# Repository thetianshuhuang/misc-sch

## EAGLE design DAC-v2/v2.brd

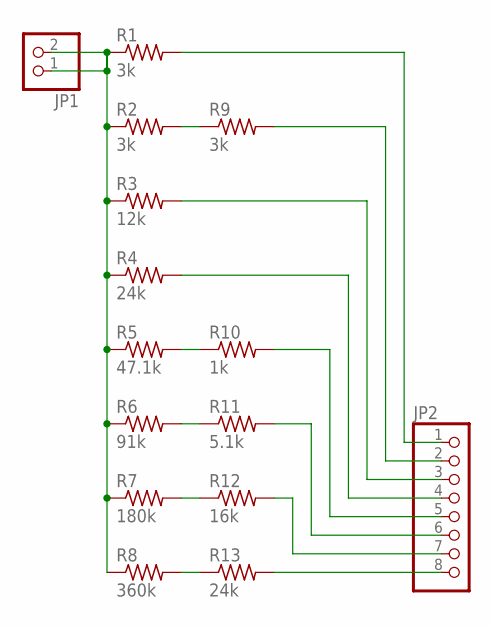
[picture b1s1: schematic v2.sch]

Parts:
JP1: PINHD-1X2; 1X02
JP2: PINHD-1X8; 1X08
R1, R2, R9: 3k; 0309/10
R3: 12k; 0309/10
R4, R13: 24k; 0309/10
R5: 47.1k; 0309/10
R6: 91k; 0309/10
R7: 180k; 0309/10
R8: 360k; 0309/10
R10: 1k; 0309/10
R11: 5.1k; 0309/10
R12: 16k; 0309/10

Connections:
unnamed: JP1.1, JP1.2, R1.1, R2.1, R3.1, R4.1, R5.1, R6.1, R7.1, R8.1
unnamed: R7.2, R12.1
unnamed: R8.2, R13.1
unnamed: JP2.8, R13.2
unnamed: R2.2, R9.1
unnamed: R5.2, R10.1
unnamed: R6.2, R11.1
unnamed: JP2.1, R1.2
unnamed: JP2.2, R9.2
unnamed: JP2.3, R3.2
unnamed: JP2.4, R4.2
unnamed: JP2.5, R10.2
unnamed: JP2.6, R11.2
unnamed: JP2.7, R12.2

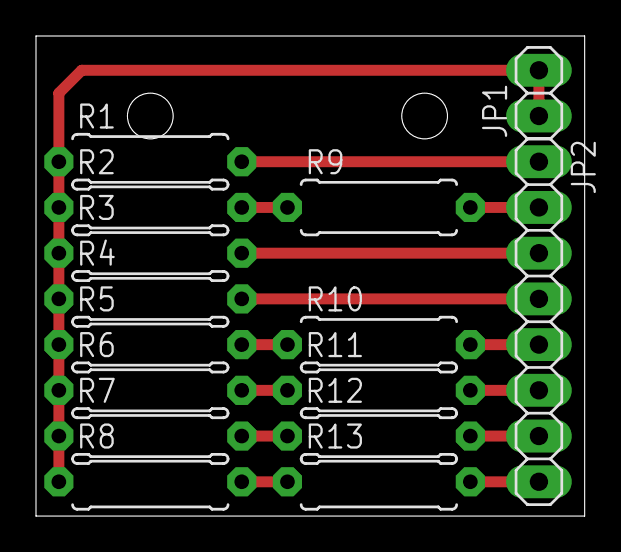
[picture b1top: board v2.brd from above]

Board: 2 copper layers, 30.5 x 26.7 mm, 15 parts (0 on the bottom side), 14 nets.

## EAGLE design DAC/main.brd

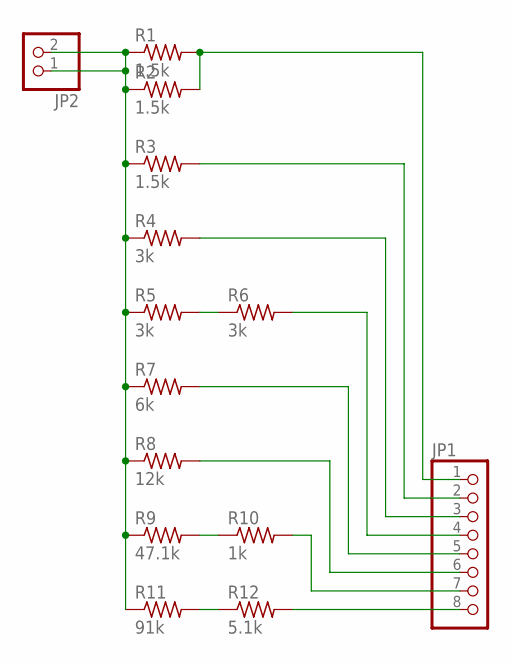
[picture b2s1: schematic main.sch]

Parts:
JP1: PINHD-1X8; 1X08
JP2: PINHD-1X2; 1X02
R1, R2, R3: 1.5k; 0309/10
R4, R5, R6: 3k; 0309/10
R7: 6k; 0309/10
R8: 12k; 0309/10
R9: 47.1k; 0309/10
R10: 1k; 0309/10
R11: 91k; 0309/10
R12: 5.1k; 0309/10

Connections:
unnamed: JP2.1, JP2.2, R1.1, R2.1, R3.1, R4.1, R5.1, R7.1, R8.1, R9.1, R11.1
unnamed: JP1.1, R1.2, R2.2
unnamed: JP1.2, R3.2
unnamed: JP1.8, R12.2
unnamed: R5.2, R6.1
unnamed: R9.2, R10.1
unnamed: R11.2, R12.1
unnamed: JP1.3, R4.2
unnamed: JP1.4, R6.2
unnamed: JP1.5, R7.2
unnamed: JP1.6, R8.2
unnamed: JP1.7, R10.2

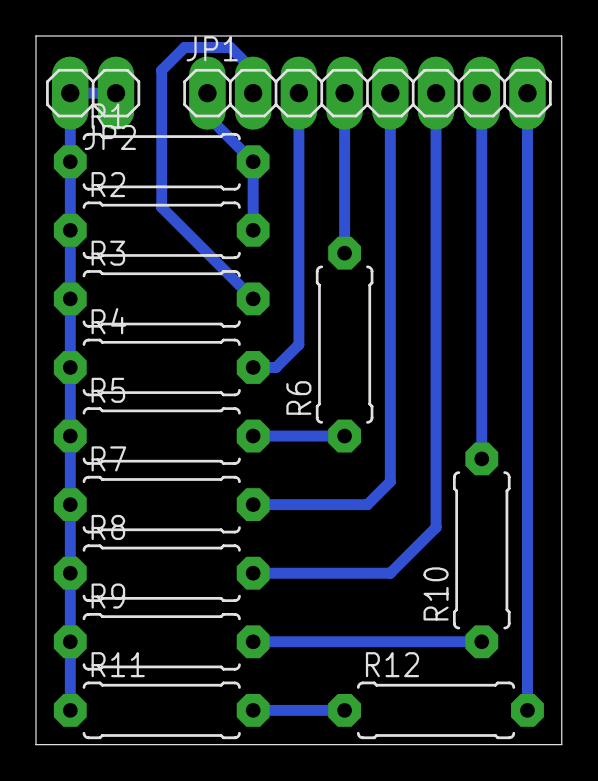
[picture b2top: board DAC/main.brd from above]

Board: 2 copper layers, 29.2 x 39.4 mm, 14 parts (0 on the bottom side), 12 nets.

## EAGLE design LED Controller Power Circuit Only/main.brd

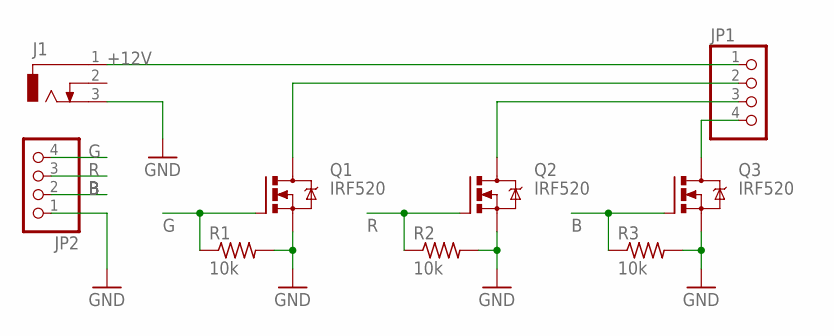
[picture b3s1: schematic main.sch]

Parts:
J1: DCJ0303
JP1, JP2: PINHD-1X4; 1X04
Q1, Q2, Q3: IRF520; TO220BV
R1, R2, R3: 10k; 0207/7

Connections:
+12V: J1.1, JP1.1
B: JP2.2, Q3.G, R3.1
G: JP2.4, Q1.G, R1.1
GND: J1.3, JP2.1, Q1.S, Q2.S, Q3.S, R1.2, R2.2, R3.2
unnamed: JP1.4, Q3.D
unnamed: JP1.3, Q2.D
unnamed: JP1.2, Q1.D
R: JP2.3, Q2.G, R2.1

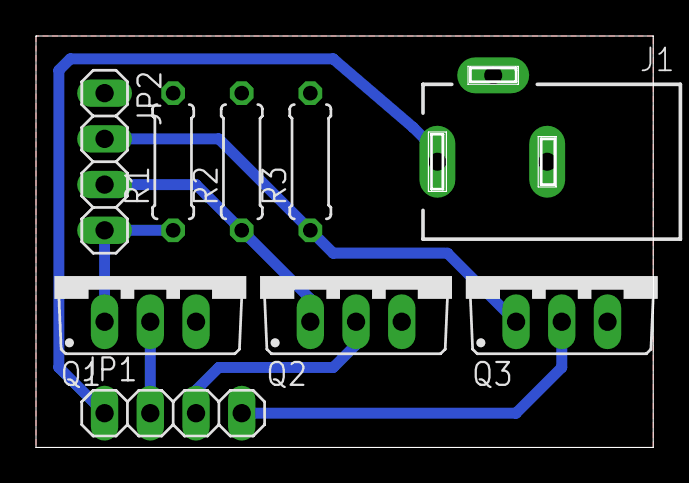
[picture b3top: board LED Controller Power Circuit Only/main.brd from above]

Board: 2 copper layers, 34.3 x 22.9 mm, 9 parts (0 on the bottom side), 8 nets.

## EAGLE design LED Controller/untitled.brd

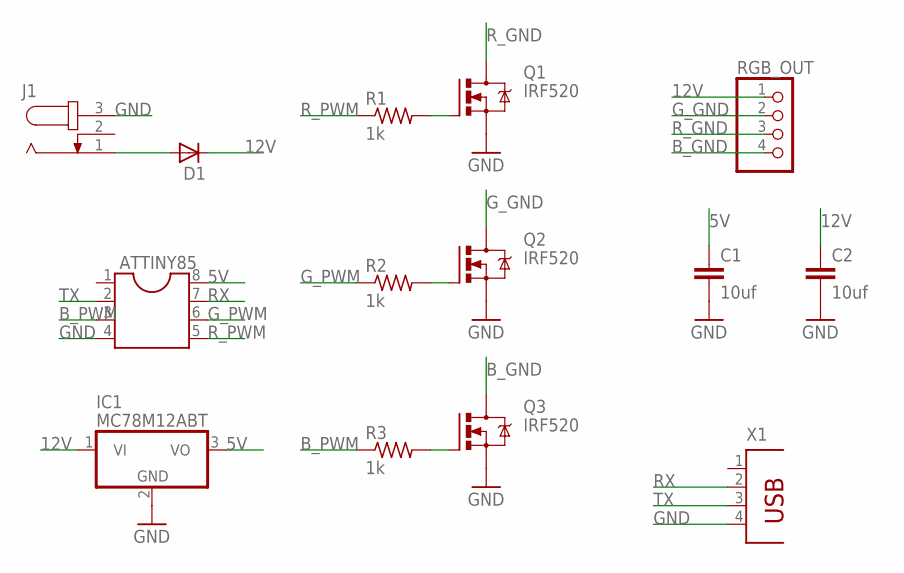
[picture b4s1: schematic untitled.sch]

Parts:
ATTINY85: DIL8S; SOCKET-08
C1, C2: 10uf; C050-045X075
D1: DIODE_E-DO35-7; DIODE_DO35-7
IC1: MC78M12ABT; TO220V
J1: JACK-PLUG0; SPC4077
Q1, Q2, Q3: IRF520; TO220BV
R1, R2, R3: 1k; 0207/10
RGB_OUT: PINHD-1X4; 1X04
X1: PN87520

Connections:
5V: ATTINY85.8, C1.1, IC1.3 (VO)
12V: C2.1, D1.C (A), IC1.1 (VI), RGB_OUT.1
B_GND: Q3.D, RGB_OUT.4
B_PWM: ATTINY85.3, R3.1
GND: ATTINY85.4, C1.2, C2.2, IC1.2 (GND), J1.3, Q1.S, Q2.S, Q3.S, X1.4
G_GND: Q2.D, RGB_OUT.2
G_PWM: ATTINY85.6, R2.1
unnamed: D1.A (C), J1.1
unnamed: Q1.G, R1.2
unnamed: Q2.G, R2.2
unnamed: Q3.G, R3.2
RX: ATTINY85.7, X1.2
R_GND: Q1.D, RGB_OUT.3
R_PWM: ATTINY85.5, R1.1
TX: ATTINY85.2, X1.3

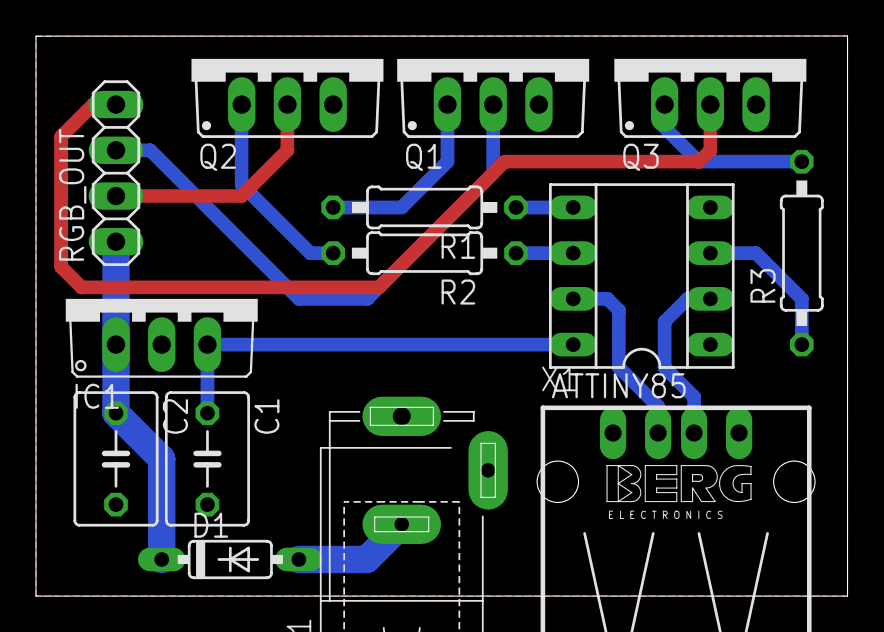
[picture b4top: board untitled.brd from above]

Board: 2 copper layers, 45.1 x 31.1 mm, 14 parts (0 on the bottom side), 15 nets.

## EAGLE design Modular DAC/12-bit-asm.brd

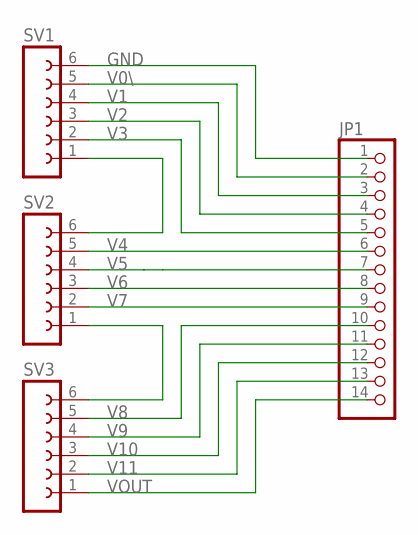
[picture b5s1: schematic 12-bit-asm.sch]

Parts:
JP1: PINHD-1X14; 1X14
SV1, SV2, SV3: FE06-1; FE06

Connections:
GND: JP1.1, SV1.6
unnamed: SV1.1, SV2.6
unnamed: SV2.1, SV3.6
V0\: JP1.2, SV1.5
V1: JP1.3, SV1.4
V2: JP1.4, SV1.3
V3: JP1.5, SV1.2
V4: JP1.6, SV2.5
V5: JP1.7, SV2.4
V6: JP1.8, SV2.3
V7: JP1.9, SV2.2
V8: JP1.10, SV3.5
V9: JP1.11, SV3.4
V10: JP1.12, SV3.3
V11: JP1.13, SV3.2
VOUT: JP1.14, SV3.1

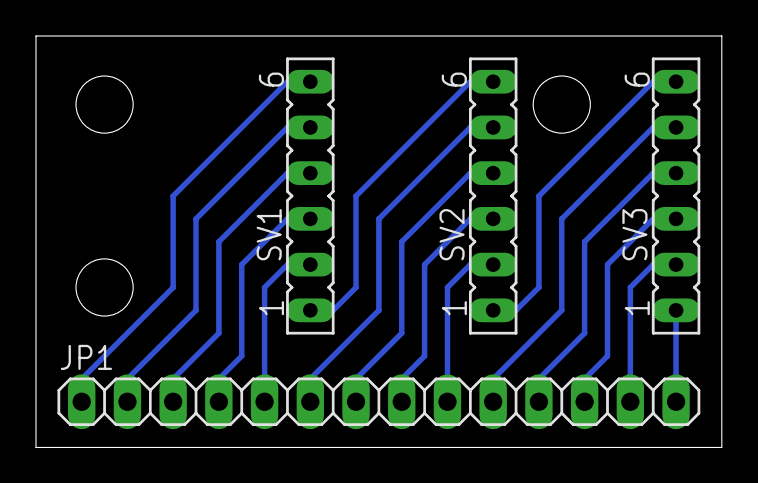
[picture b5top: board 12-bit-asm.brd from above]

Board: 2 copper layers, 38.1 x 22.9 mm, 4 parts (0 on the bottom side), 16 nets.

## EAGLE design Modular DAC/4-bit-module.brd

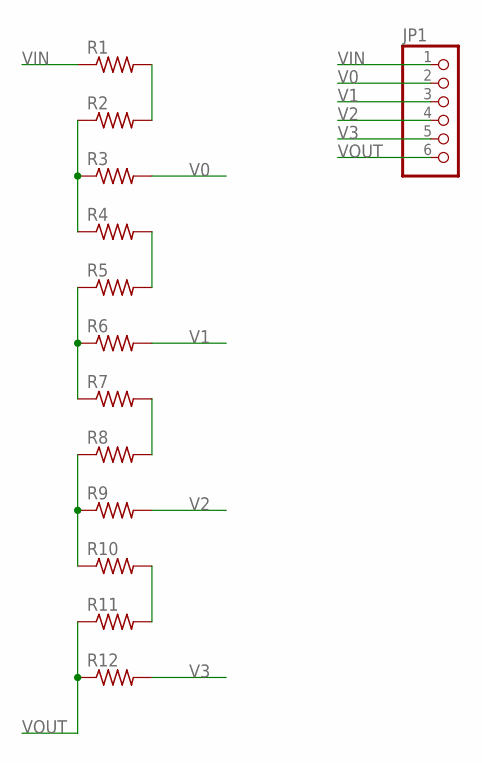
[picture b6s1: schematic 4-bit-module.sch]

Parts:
JP1: PINHD-1X6/90; 1X06/90
R1, R2, R3, R4, R5, R6, R7, R8, R9, R10, R11, R12: R-US_0204/7; 0204/7

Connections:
unnamed: R1.2, R2.2
unnamed: R2.1, R3.1, R4.1
unnamed: R4.2, R5.2
unnamed: R5.1, R6.1, R7.1
unnamed: R7.2, R8.2
unnamed: R8.1, R9.1, R10.1
unnamed: R10.2, R11.2
V0: JP1.2, R3.2
V1: JP1.3, R6.2
V2: JP1.4, R9.2
V3: JP1.5, R12.2
VIN: JP1.1, R1.1
VOUT: JP1.6, R11.1, R12.1

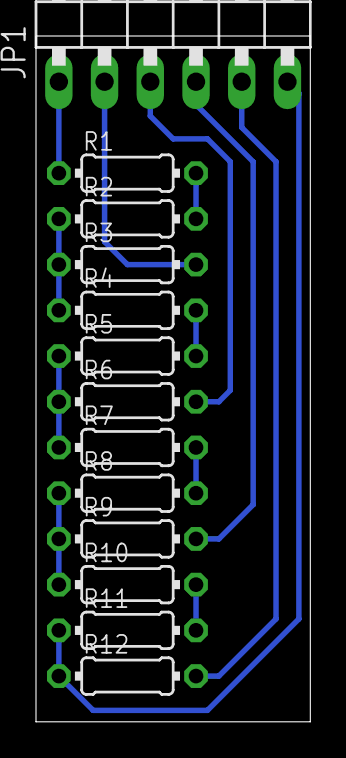
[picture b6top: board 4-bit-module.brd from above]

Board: 2 copper layers, 15.2 x 38.1 mm, 13 parts (0 on the bottom side), 13 nets.
